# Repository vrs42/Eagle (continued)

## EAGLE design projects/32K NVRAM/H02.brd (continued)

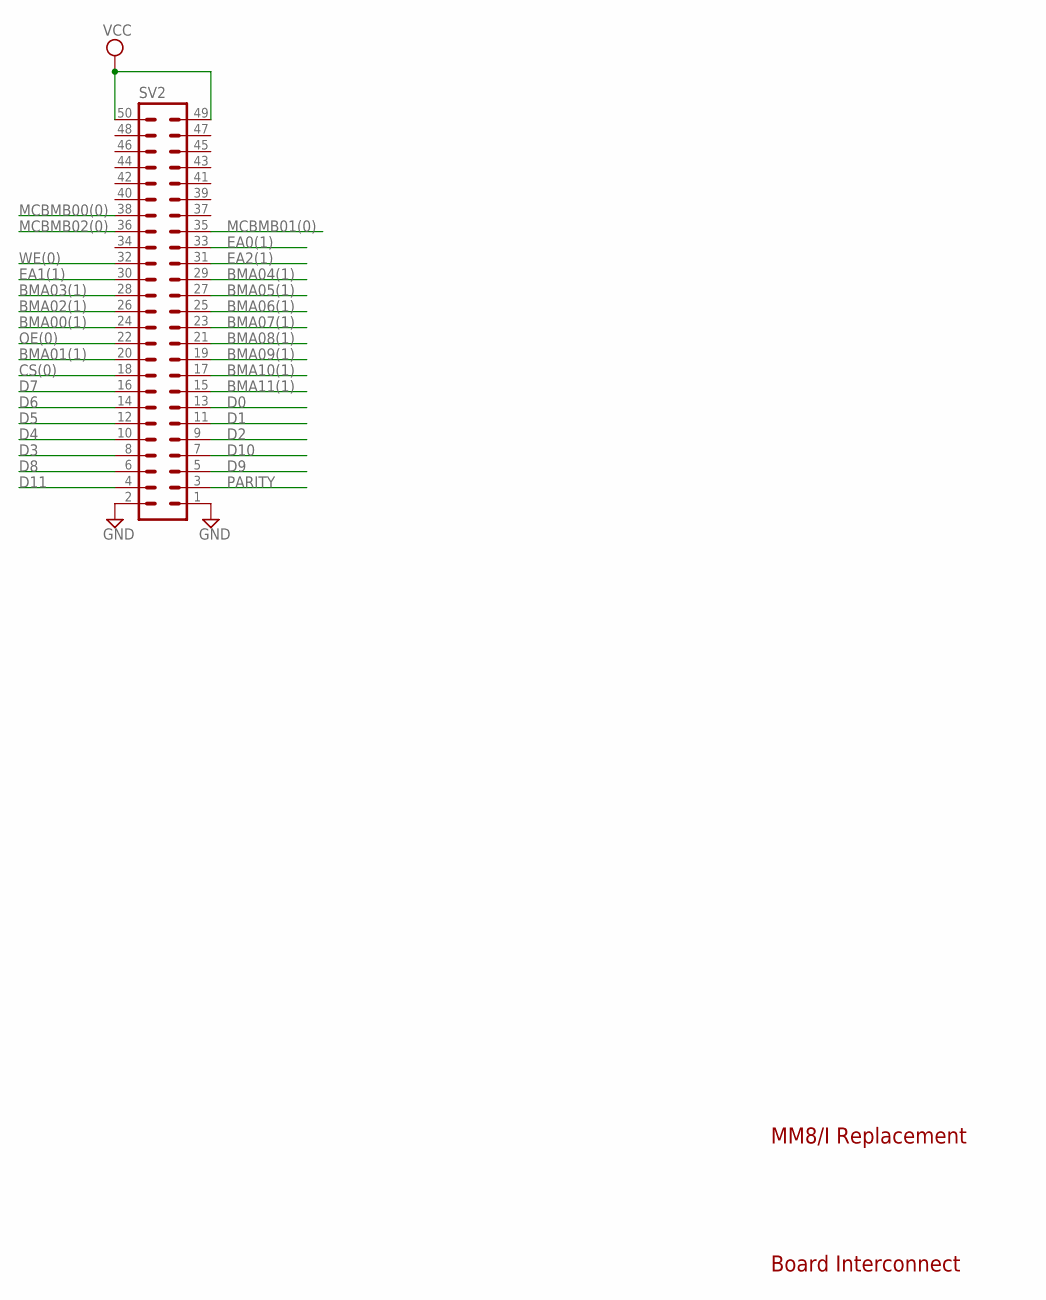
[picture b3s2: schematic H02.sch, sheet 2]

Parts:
SV2: ML50L

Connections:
BMA00(1): SV2.24; also elsewhere on the board
BMA01(1): SV2.20; also elsewhere on the board
BMA02(1): SV2.26; also elsewhere on the board
BMA03(1): SV2.28; also elsewhere on the board
BMA04(1): SV2.29; also elsewhere on the board
BMA05(1): SV2.27; also elsewhere on the board
BMA06(1): SV2.25; also elsewhere on the board
BMA07(1): SV2.23; also elsewhere on the board
BMA08(1): SV2.21; also elsewhere on the board
BMA09(1): SV2.19; also elsewhere on the board
BMA10(1): SV2.17; also elsewhere on the board
BMA11(1): SV2.15; also elsewhere on the board
CS(0): SV2.18; also elsewhere on the board
D0: SV2.13; also elsewhere on the board
D1: SV2.11; also elsewhere on the board
D2: SV2.9; also elsewhere on the board
D3: SV2.8; also elsewhere on the board
D4: SV2.10; also elsewhere on the board
D5: SV2.12; also elsewhere on the board
D6: SV2.14; also elsewhere on the board
D7: SV2.16; also elsewhere on the board
D8: SV2.6; also elsewhere on the board
D9: SV2.5; also elsewhere on the board
D10: SV2.7; also elsewhere on the board
D11: SV2.4; also elsewhere on the board
EA0(1): SV2.33; also elsewhere on the board
EA1(1): SV2.30; also elsewhere on the board
EA2(1): SV2.31; also elsewhere on the board
GND: SV2.1, SV2.2; also elsewhere on the board
MCBMB00(0): SV2.38; also elsewhere on the board
MCBMB01(0): SV2.35; also elsewhere on the board
MCBMB02(0): SV2.36; also elsewhere on the board
OE(0): SV2.22; also elsewhere on the board
PARITY: SV2.3; also elsewhere on the board
VCC: SV2.49, SV2.50; also elsewhere on the board
WE(0): SV2.32; also elsewhere on the board

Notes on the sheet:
Board Interconnect
MM8/I Replacement

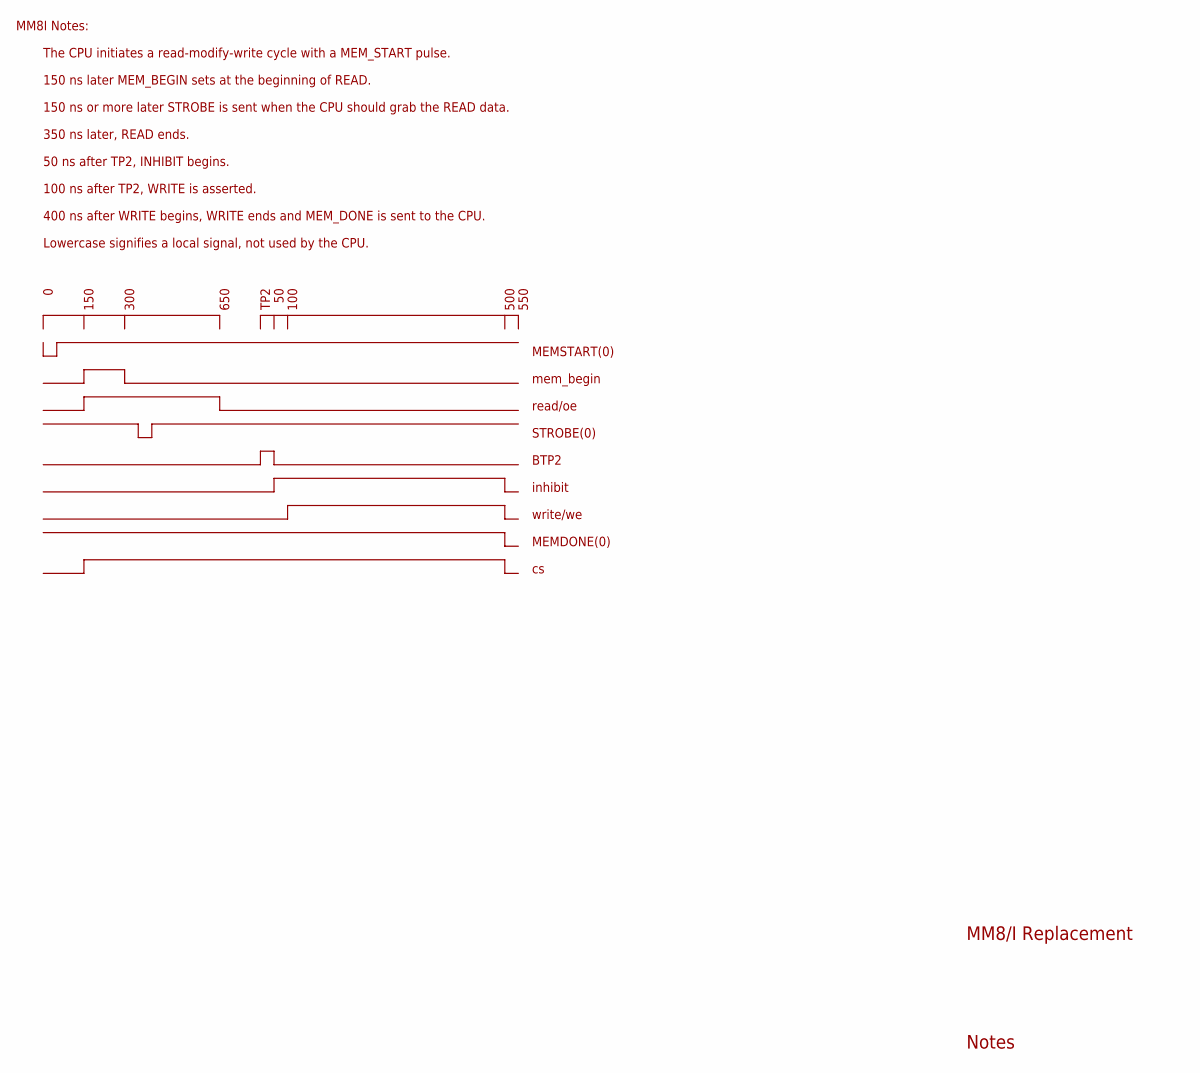
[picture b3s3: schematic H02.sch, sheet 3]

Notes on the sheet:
Notes
The CPU initiates a read-modify-write cycle with a MEM_START pulse.
150 ns later MEM_BEGIN sets at the beginning of READ.
150 ns or more later STROBE is sent when the CPU should grab the READ data.
50 ns after TP2, INHIBIT begins.
100 ns after TP2, WRITE is asserted.
400 ns after WRITE begins, WRITE ends and MEM_DONE is sent to the CPU.
350 ns later, READ ends.
150
300
650
TP2
100
500
MEMSTART(0)
mem_begin
read/oe
STROBE(0)
BTP2
inhibit
write/we
MEMDONE(0)
Lowercase signifies a local signal, not used by the CPU.
550
MM8I Notes:
MM8/I Replacement

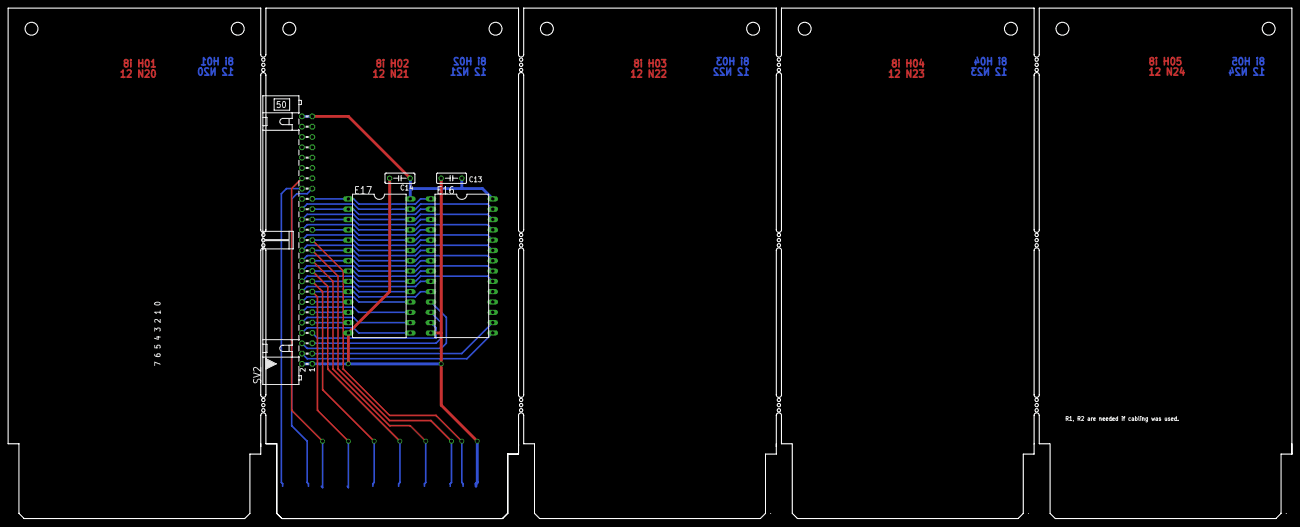
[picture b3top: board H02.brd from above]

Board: 2 copper layers, 316.2 x 125.7 mm, 7 parts (0 on the bottom side), 36 nets.

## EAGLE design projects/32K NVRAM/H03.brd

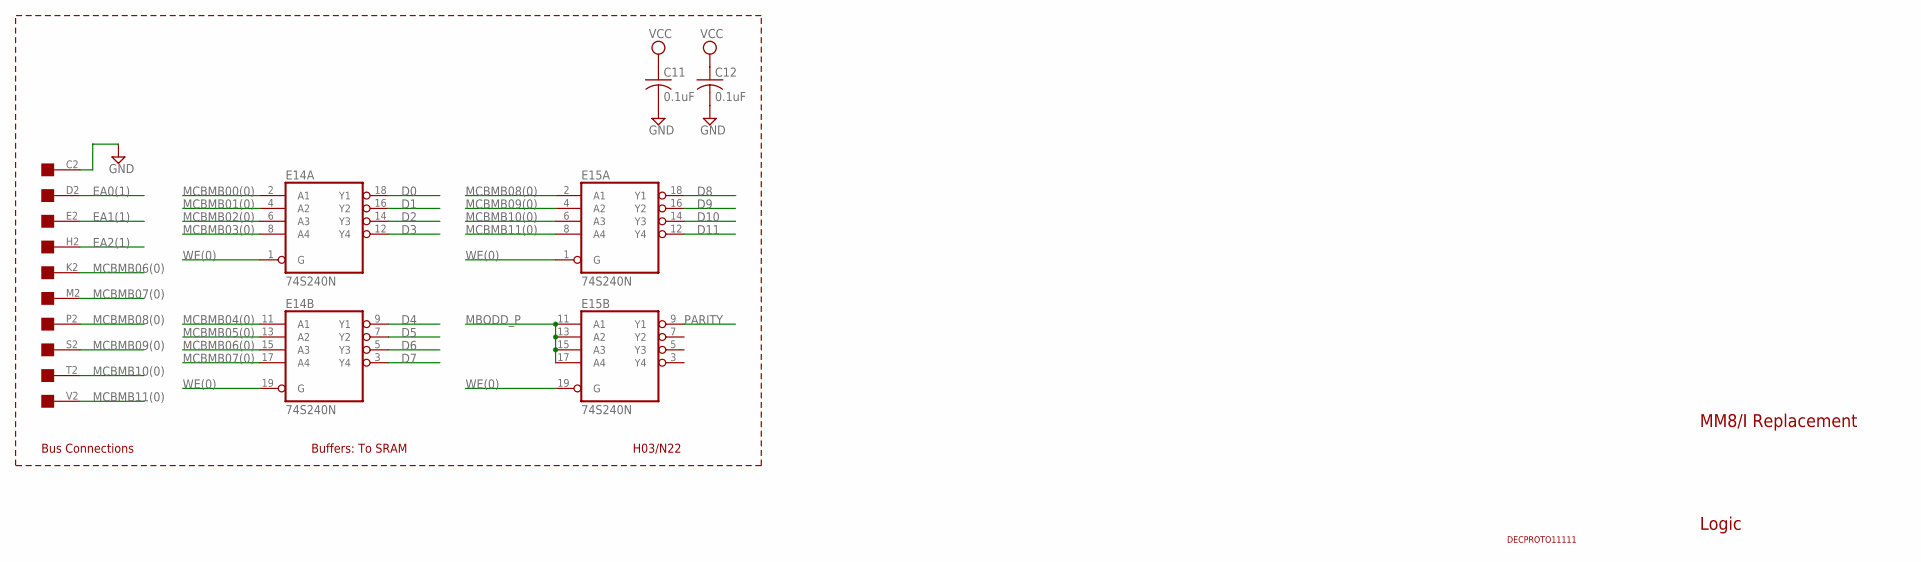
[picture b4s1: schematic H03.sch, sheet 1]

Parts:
C11, C12: 0.1uF; C050-025X075
E14, E15: 74S240N; DIL20
H03: EDGE-CON1
U$6: DECPROTO11111

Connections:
D0: E14.18 (Y1); also elsewhere on the board
D1: E14.16 (Y2); also elsewhere on the board
D2: E14.14 (Y3); also elsewhere on the board
D3: E14.12 (Y4); also elsewhere on the board
D4: E14.9 (Y1); also elsewhere on the board
D5: E14.7 (Y2); also elsewhere on the board
D6: E14.5 (Y3); also elsewhere on the board
D7: E14.3 (Y4); also elsewhere on the board
D8: E15.18 (Y1); also elsewhere on the board
D9: E15.16 (Y2); also elsewhere on the board
D10: E15.14 (Y3); also elsewhere on the board
D11: E15.12 (Y4); also elsewhere on the board
EA0(1): H03.D2; also elsewhere on the board
EA1(1): H03.E2; also elsewhere on the board
EA2(1): H03.H2; also elsewhere on the board
GND: C11.2, C12.2, E14.10 (GND), E15.10 (GND), H03.C2; also elsewhere on the board
MBODD_P: E15.11 (A1), E15.13 (A2), E15.15 (A3), E15.17 (A4); also elsewhere on the board
MCBMB00(0): E14.2 (A1); also elsewhere on the board
MCBMB01(0): E14.4 (A2); also elsewhere on the board
MCBMB02(0): E14.6 (A3); also elsewhere on the board
MCBMB03(0): E14.8 (A4); also elsewhere on the board
MCBMB04(0): E14.11 (A1); also elsewhere on the board
MCBMB05(0): E14.13 (A2); also elsewhere on the board
MCBMB06(0): E14.15 (A3), H03.K2
MCBMB07(0): E14.17 (A4), H03.M2
MCBMB08(0): E15.2 (A1), H03.P2
MCBMB09(0): E15.4 (A2), H03.S2
MCBMB10(0): E15.6 (A3), H03.T2
MCBMB11(0): E15.8 (A4), H03.V2
PARITY: E15.9 (Y1); also elsewhere on the board
VCC: C11.1, C12.1, E14.20 (VCC), E15.20 (VCC); also elsewhere on the board
WE(0): E14.1 (G), E14.19 (G), E15.1 (G), E15.19 (G); also elsewhere on the board

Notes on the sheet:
H03/N22
MM8/I Replacement
Buffers: To SRAM
Logic
Bus Connections

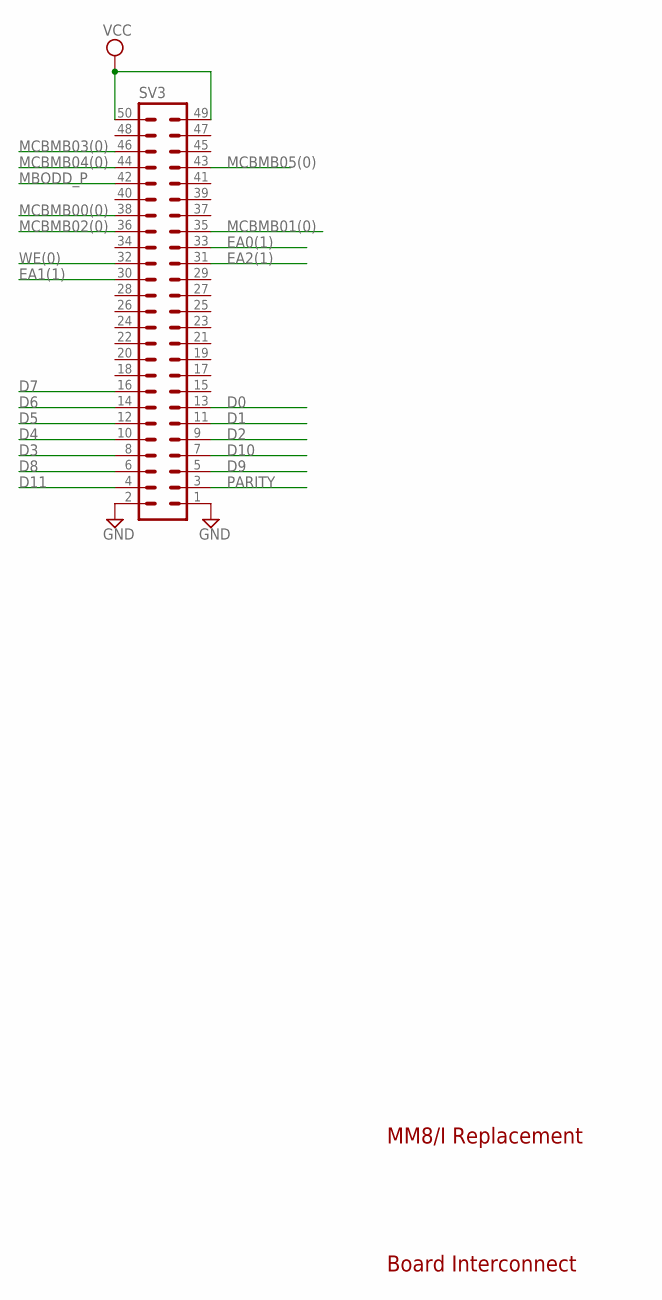
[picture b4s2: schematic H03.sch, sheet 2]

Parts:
SV3: ML50L

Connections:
D0: SV3.13; also elsewhere on the board
D1: SV3.11; also elsewhere on the board
D2: SV3.9; also elsewhere on the board
D3: SV3.8; also elsewhere on the board
D4: SV3.10; also elsewhere on the board
D5: SV3.12; also elsewhere on the board
D6: SV3.14; also elsewhere on the board
D7: SV3.16; also elsewhere on the board
D8: SV3.6; also elsewhere on the board
D9: SV3.5; also elsewhere on the board
D10: SV3.7; also elsewhere on the board
D11: SV3.4; also elsewhere on the board
EA0(1): SV3.33; also elsewhere on the board
EA1(1): SV3.30; also elsewhere on the board
EA2(1): SV3.31; also elsewhere on the board
GND: SV3.1, SV3.2; also elsewhere on the board
MBODD_P: SV3.42; also elsewhere on the board
MCBMB00(0): SV3.38; also elsewhere on the board
MCBMB01(0): SV3.35; also elsewhere on the board
MCBMB02(0): SV3.36; also elsewhere on the board
MCBMB03(0): SV3.46; also elsewhere on the board
MCBMB04(0): SV3.44; also elsewhere on the board
MCBMB05(0): SV3.43; also elsewhere on the board
PARITY: SV3.3; also elsewhere on the board
VCC: SV3.49, SV3.50; also elsewhere on the board
WE(0): SV3.32; also elsewhere on the board

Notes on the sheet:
Board Interconnect
MM8/I Replacement

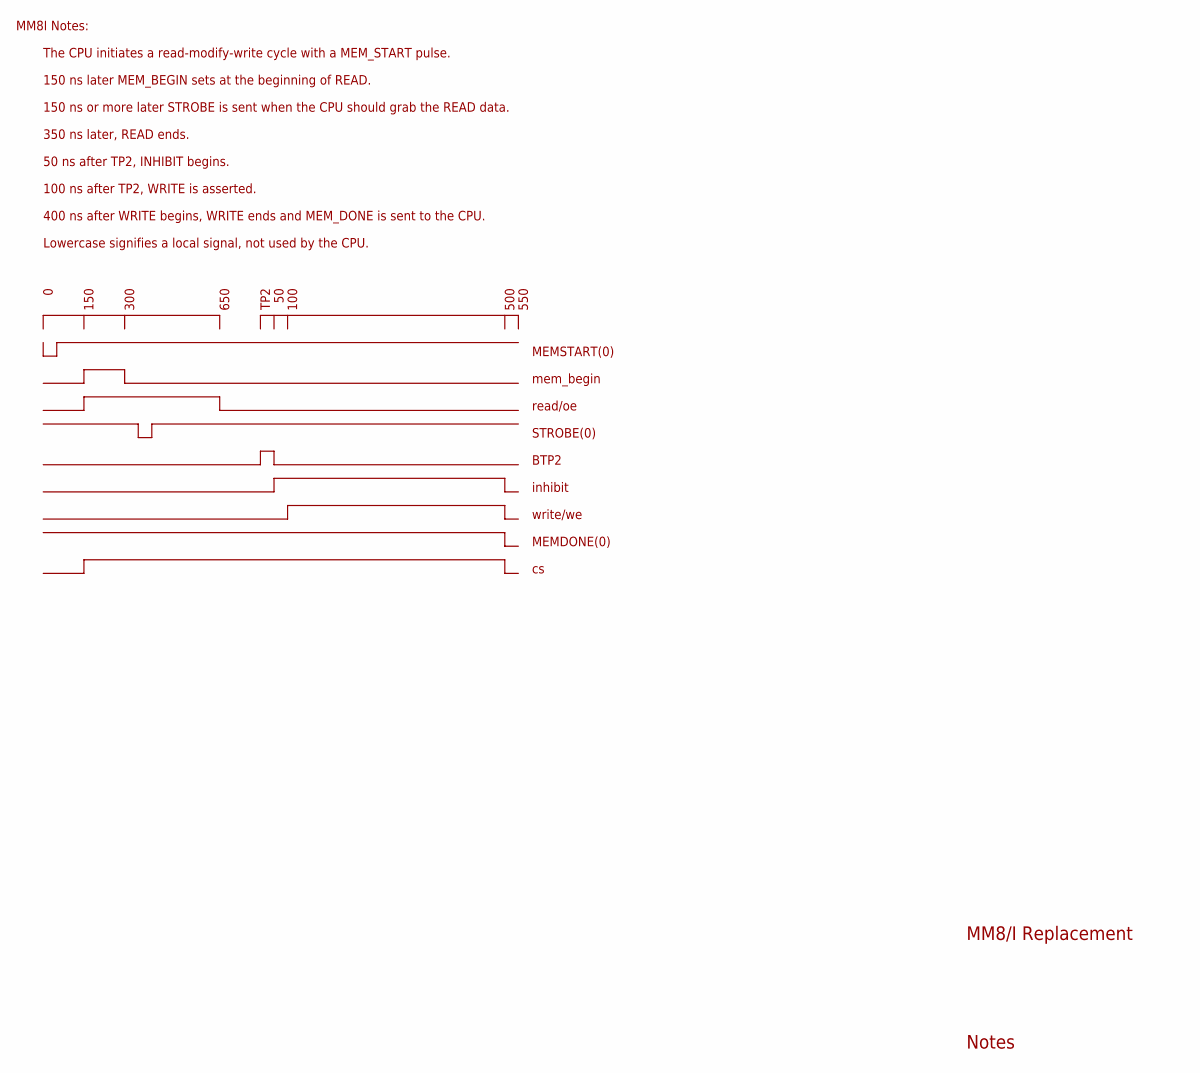
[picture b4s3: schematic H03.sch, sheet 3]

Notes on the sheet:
Notes
The CPU initiates a read-modify-write cycle with a MEM_START pulse.
150 ns later MEM_BEGIN sets at the beginning of READ.
150 ns or more later STROBE is sent when the CPU should grab the READ data.
50 ns after TP2, INHIBIT begins.
100 ns after TP2, WRITE is asserted.
400 ns after WRITE begins, WRITE ends and MEM_DONE is sent to the CPU.
350 ns later, READ ends.
150
300
650
TP2
100
500
MEMSTART(0)
mem_begin
read/oe
STROBE(0)
BTP2
inhibit
write/we
MEMDONE(0)
Lowercase signifies a local signal, not used by the CPU.
550
MM8I Notes:
MM8/I Replacement

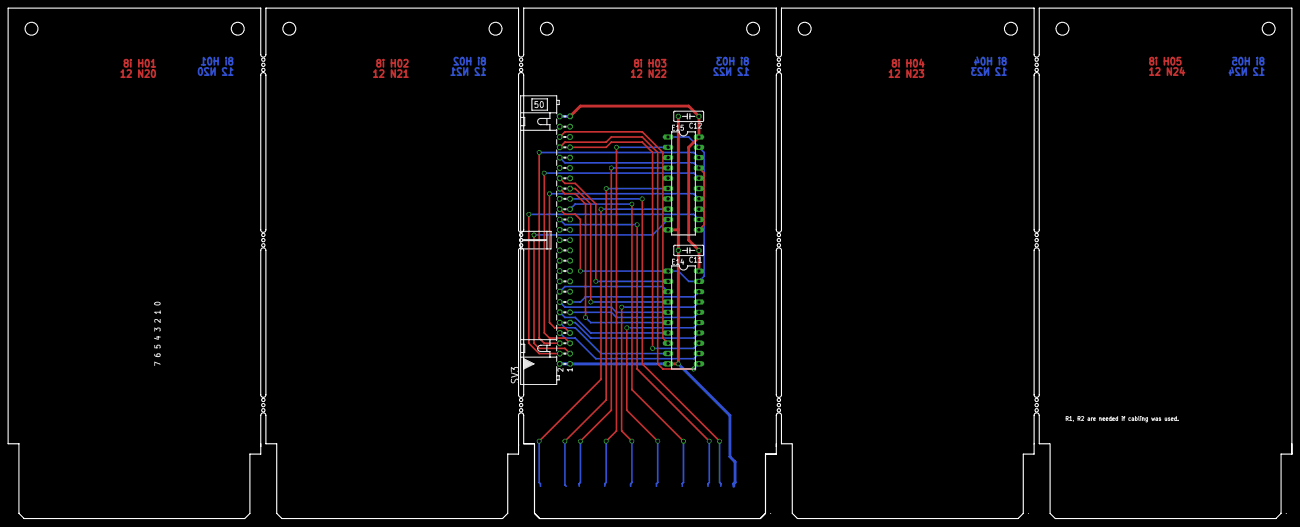
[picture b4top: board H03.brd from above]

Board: 2 copper layers, 316.2 x 125.7 mm, 7 parts (0 on the bottom side), 32 nets.

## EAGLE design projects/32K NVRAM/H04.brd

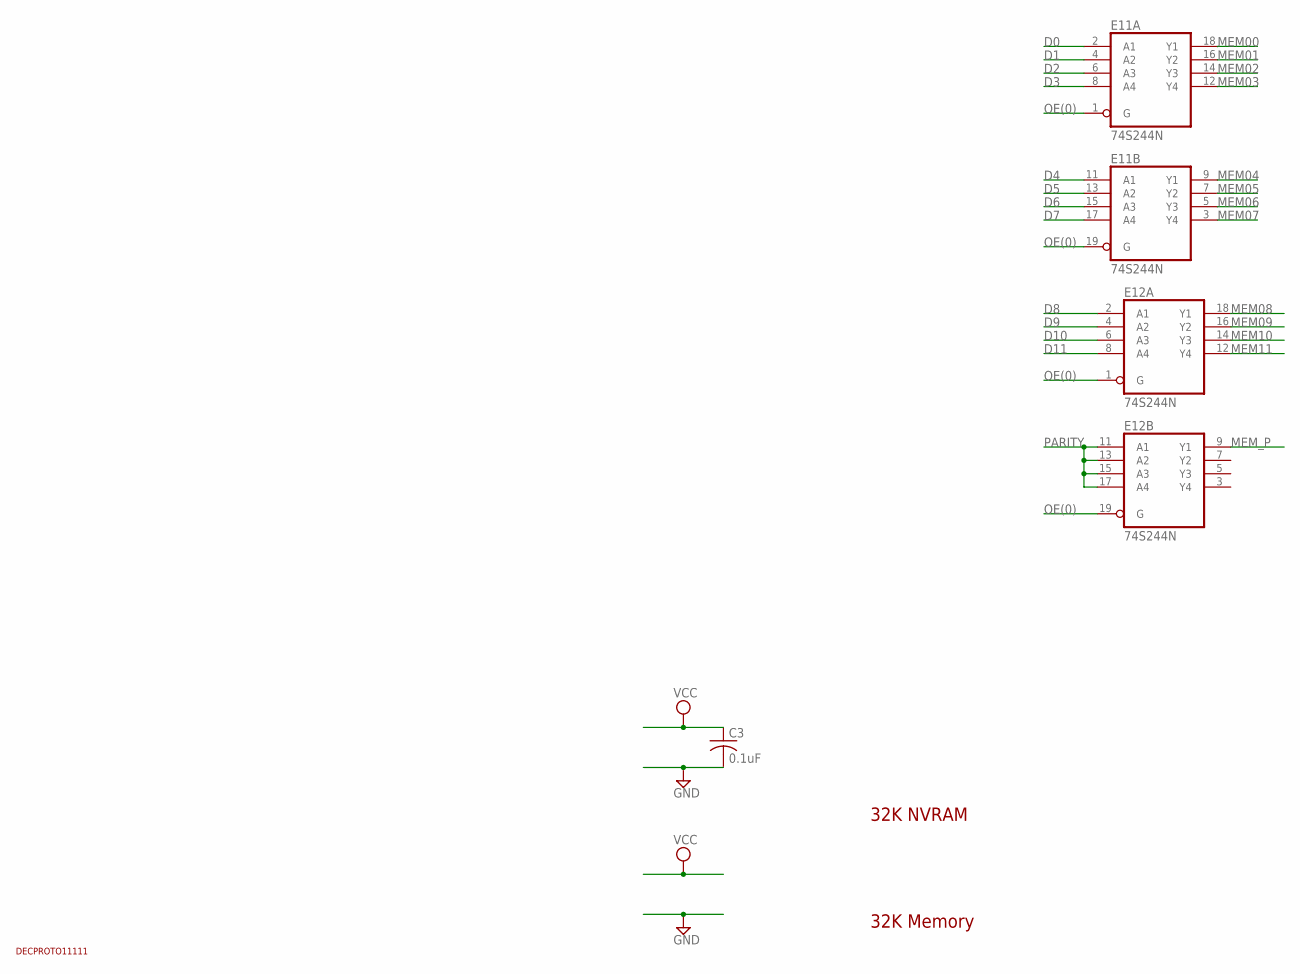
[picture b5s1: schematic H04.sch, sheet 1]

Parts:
C3: 0.1uF; C050-025X075
E11, E12: 74S244N; DIL20
U$6: DECPROTO11111

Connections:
D0: E11.2 (A1); also elsewhere on the board
D1: E11.4 (A2); also elsewhere on the board
D2: E11.6 (A3); also elsewhere on the board
D3: E11.8 (A4); also elsewhere on the board
D4: E11.11 (A1); also elsewhere on the board
D5: E11.13 (A2); also elsewhere on the board
D6: E11.15 (A3); also elsewhere on the board
D7: E11.17 (A4); also elsewhere on the board
D8: E12.2 (A1); also elsewhere on the board
D9: E12.4 (A2); also elsewhere on the board
D10: E12.6 (A3); also elsewhere on the board
D11: E12.8 (A4); also elsewhere on the board
GND: C3.2, E11.10 (GND), E12.10 (GND); also elsewhere on the board
MEM00: E11.18 (Y1); also elsewhere on the board
MEM01: E11.16 (Y2); also elsewhere on the board
MEM02: E11.14 (Y3); also elsewhere on the board
MEM03: E11.12 (Y4); also elsewhere on the board
MEM04: E11.9 (Y1); also elsewhere on the board
MEM05: E11.7 (Y2); also elsewhere on the board
MEM06: E11.5 (Y3); also elsewhere on the board
MEM07: E11.3 (Y4); also elsewhere on the board
MEM08: E12.18 (Y1); also elsewhere on the board
MEM09: E12.16 (Y2); also elsewhere on the board
MEM10: E12.14 (Y3); also elsewhere on the board
MEM11: E12.12 (Y4); also elsewhere on the board
MEM_P: E12.9 (Y1); also elsewhere on the board
OE(0): E11.1 (G), E11.19 (G), E12.1 (G), E12.19 (G); also elsewhere on the board
PARITY: E12.11 (A1), E12.13 (A2), E12.15 (A3), E12.17 (A4); also elsewhere on the board
VCC: C3.1, E11.20 (VCC), E12.20 (VCC); also elsewhere on the board

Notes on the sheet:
32K NVRAM
32K Memory

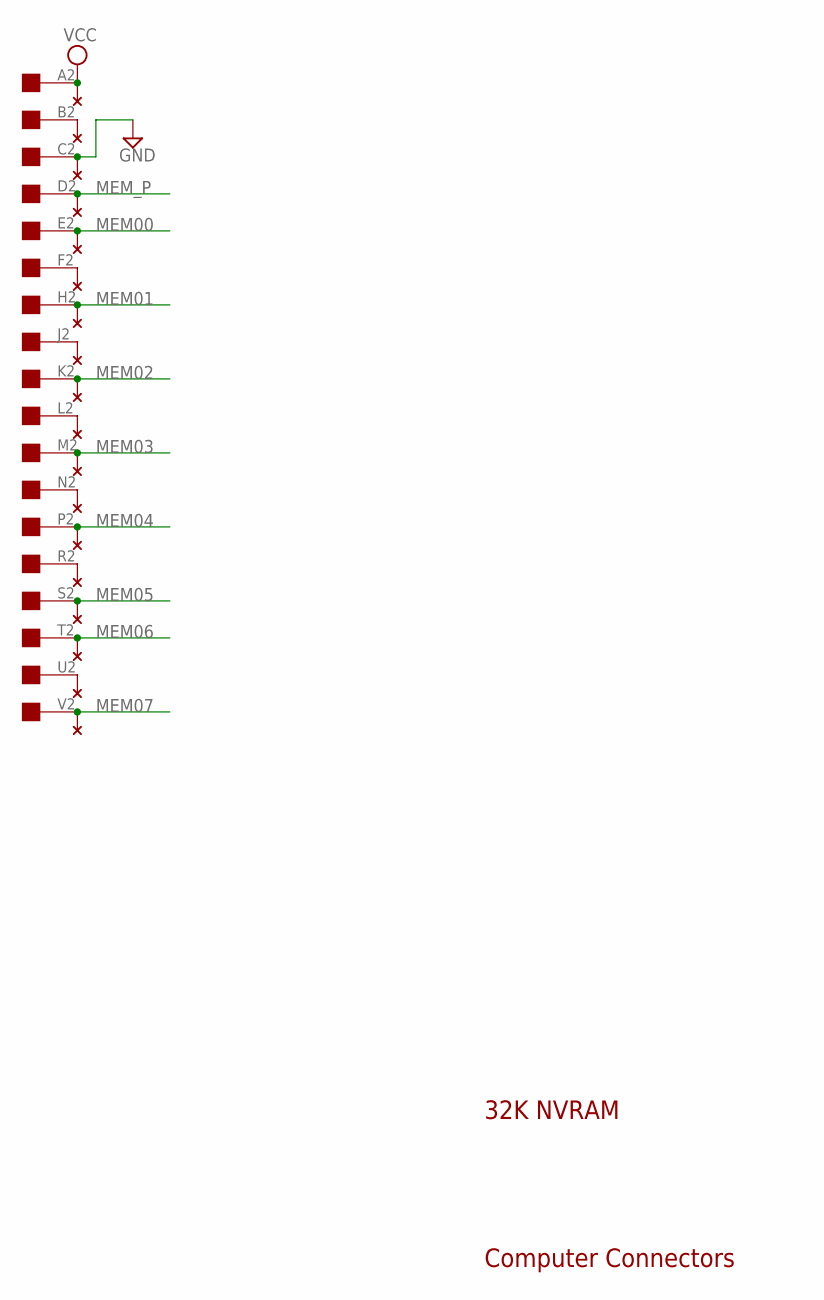
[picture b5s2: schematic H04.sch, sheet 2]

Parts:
H04: EDGE-CON1
U$4: THRU-HOLE2; THRU-HOLEB

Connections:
GND: H04.C2, U$4.C2; also elsewhere on the board
MEM00: H04.E2, U$4.E2; also elsewhere on the board
MEM01: H04.H2, U$4.H2; also elsewhere on the board
MEM02: H04.K2, U$4.K2; also elsewhere on the board
MEM03: H04.M2, U$4.M2; also elsewhere on the board
MEM04: H04.P2, U$4.P2; also elsewhere on the board
MEM05: H04.S2, U$4.S2; also elsewhere on the board
MEM06: H04.T2, U$4.T2; also elsewhere on the board
MEM07: H04.V2, U$4.V2; also elsewhere on the board
MEM_P: H04.D2, U$4.D2; also elsewhere on the board
unnamed: H04.J2, U$4.J2
unnamed: H04.L2, U$4.L2
unnamed: H04.N2, U$4.N2
unnamed: H04.F2, U$4.F2
unnamed: H04.R2, U$4.R2
unnamed: H04.B2, U$4.B2
unnamed: H04.U2, U$4.U2
VCC: H04.A2, U$4.A2; also elsewhere on the board

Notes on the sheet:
32K NVRAM
Computer Connectors

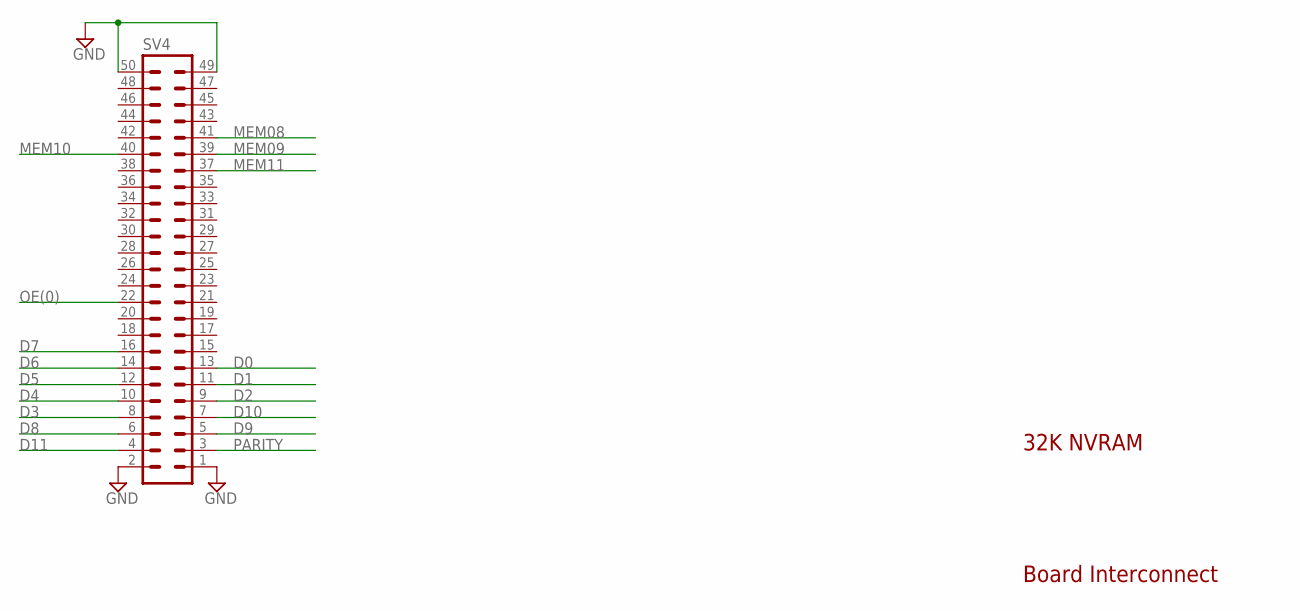
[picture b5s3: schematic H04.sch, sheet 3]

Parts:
SV4: ML50L

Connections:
D0: SV4.13; also elsewhere on the board
D1: SV4.11; also elsewhere on the board
D2: SV4.9; also elsewhere on the board
D3: SV4.8; also elsewhere on the board
D4: SV4.10; also elsewhere on the board
D5: SV4.12; also elsewhere on the board
D6: SV4.14; also elsewhere on the board
D7: SV4.16; also elsewhere on the board
D8: SV4.6; also elsewhere on the board
D9: SV4.5; also elsewhere on the board
D10: SV4.7; also elsewhere on the board
D11: SV4.4; also elsewhere on the board
GND: SV4.1, SV4.2, SV4.49, SV4.50; also elsewhere on the board
MEM08: SV4.41; also elsewhere on the board
MEM09: SV4.39; also elsewhere on the board
MEM10: SV4.40; also elsewhere on the board
MEM11: SV4.37; also elsewhere on the board
OE(0): SV4.22; also elsewhere on the board
PARITY: SV4.3; also elsewhere on the board

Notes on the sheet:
32K NVRAM
Board Interconnect

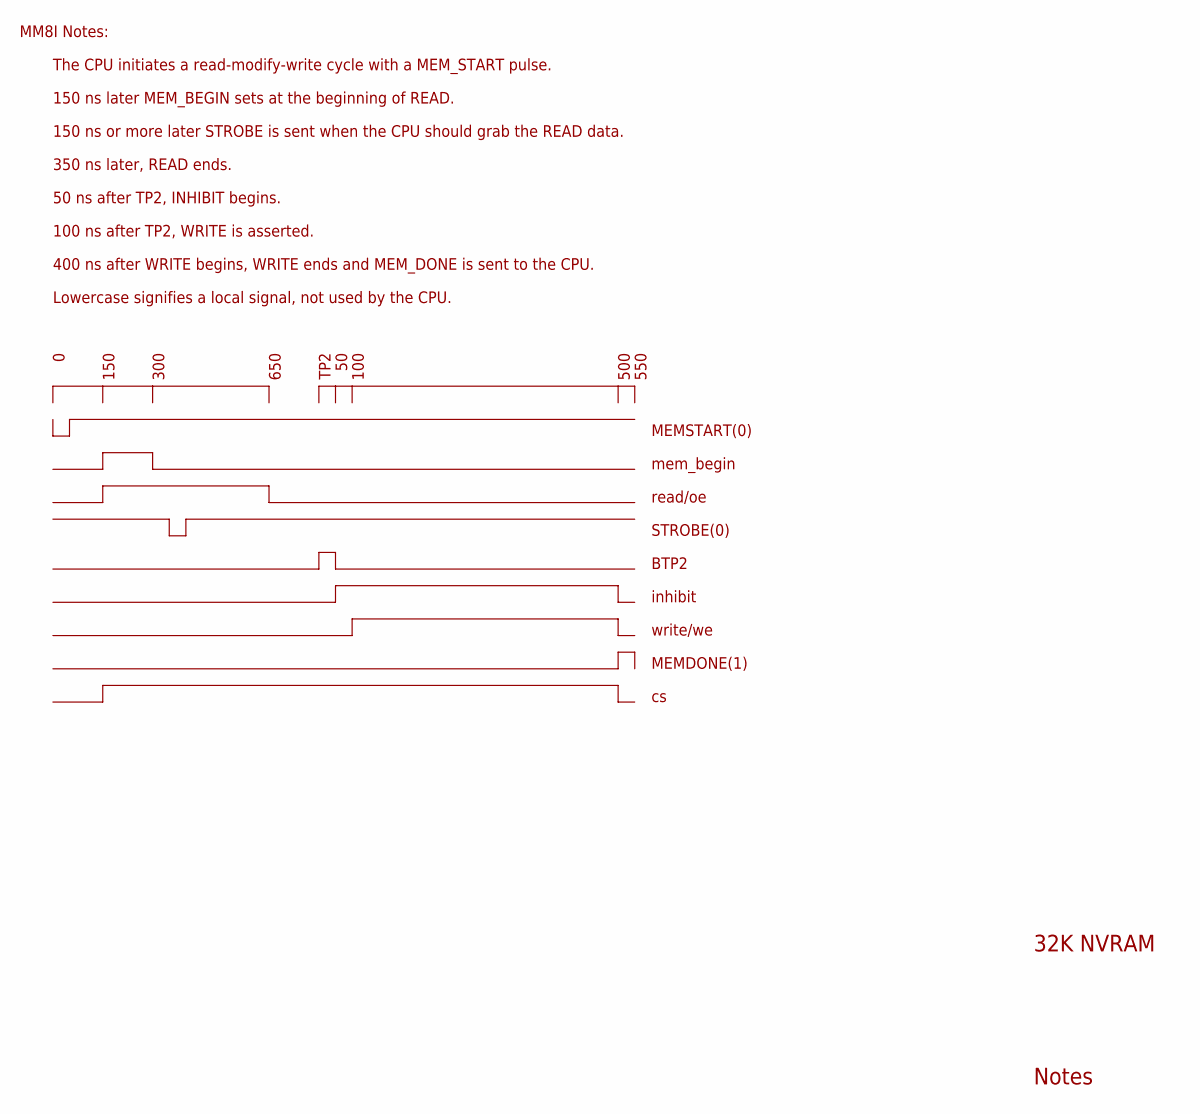
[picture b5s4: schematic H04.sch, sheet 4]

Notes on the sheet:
32K NVRAM
Notes
The CPU initiates a read-modify-write cycle with a MEM_START pulse.
150 ns later MEM_BEGIN sets at the beginning of READ.
150 ns or more later STROBE is sent when the CPU should grab the READ data.
50 ns after TP2, INHIBIT begins.
100 ns after TP2, WRITE is asserted.
400 ns after WRITE begins, WRITE ends and MEM_DONE is sent to the CPU.
350 ns later, READ ends.
150
300
650
TP2
100
500
MEMSTART(0)
mem_begin
read/oe
STROBE(0)
BTP2
inhibit
write/we
MEMDONE(1)
Lowercase signifies a local signal, not used by the CPU.
550
MM8I Notes:

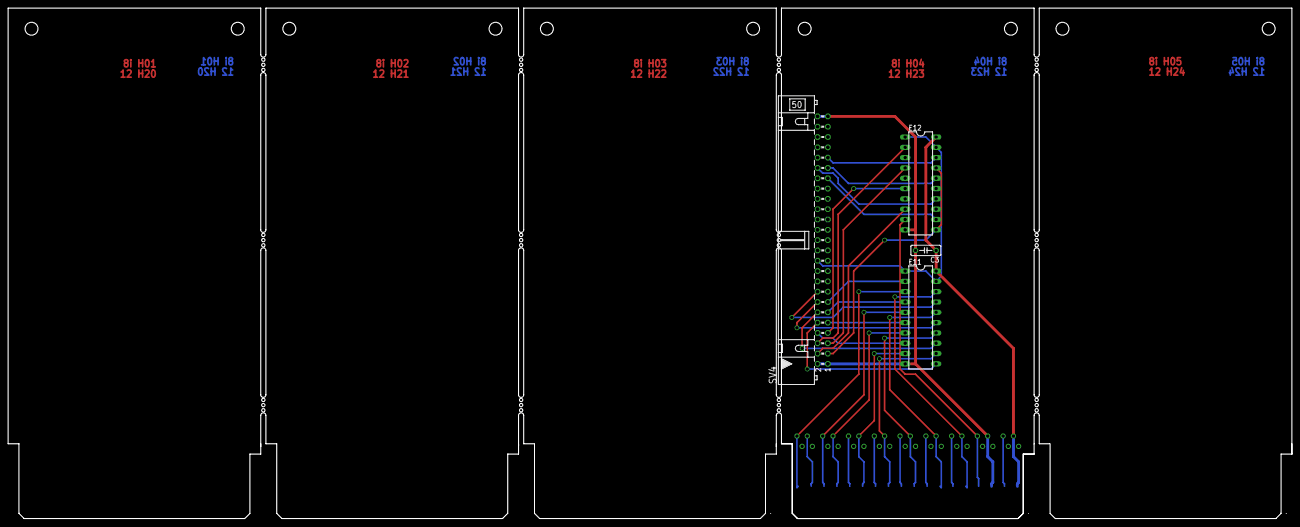
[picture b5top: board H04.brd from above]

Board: 2 copper layers, 316.2 x 125.7 mm, 7 parts (0 on the bottom side), 36 nets.

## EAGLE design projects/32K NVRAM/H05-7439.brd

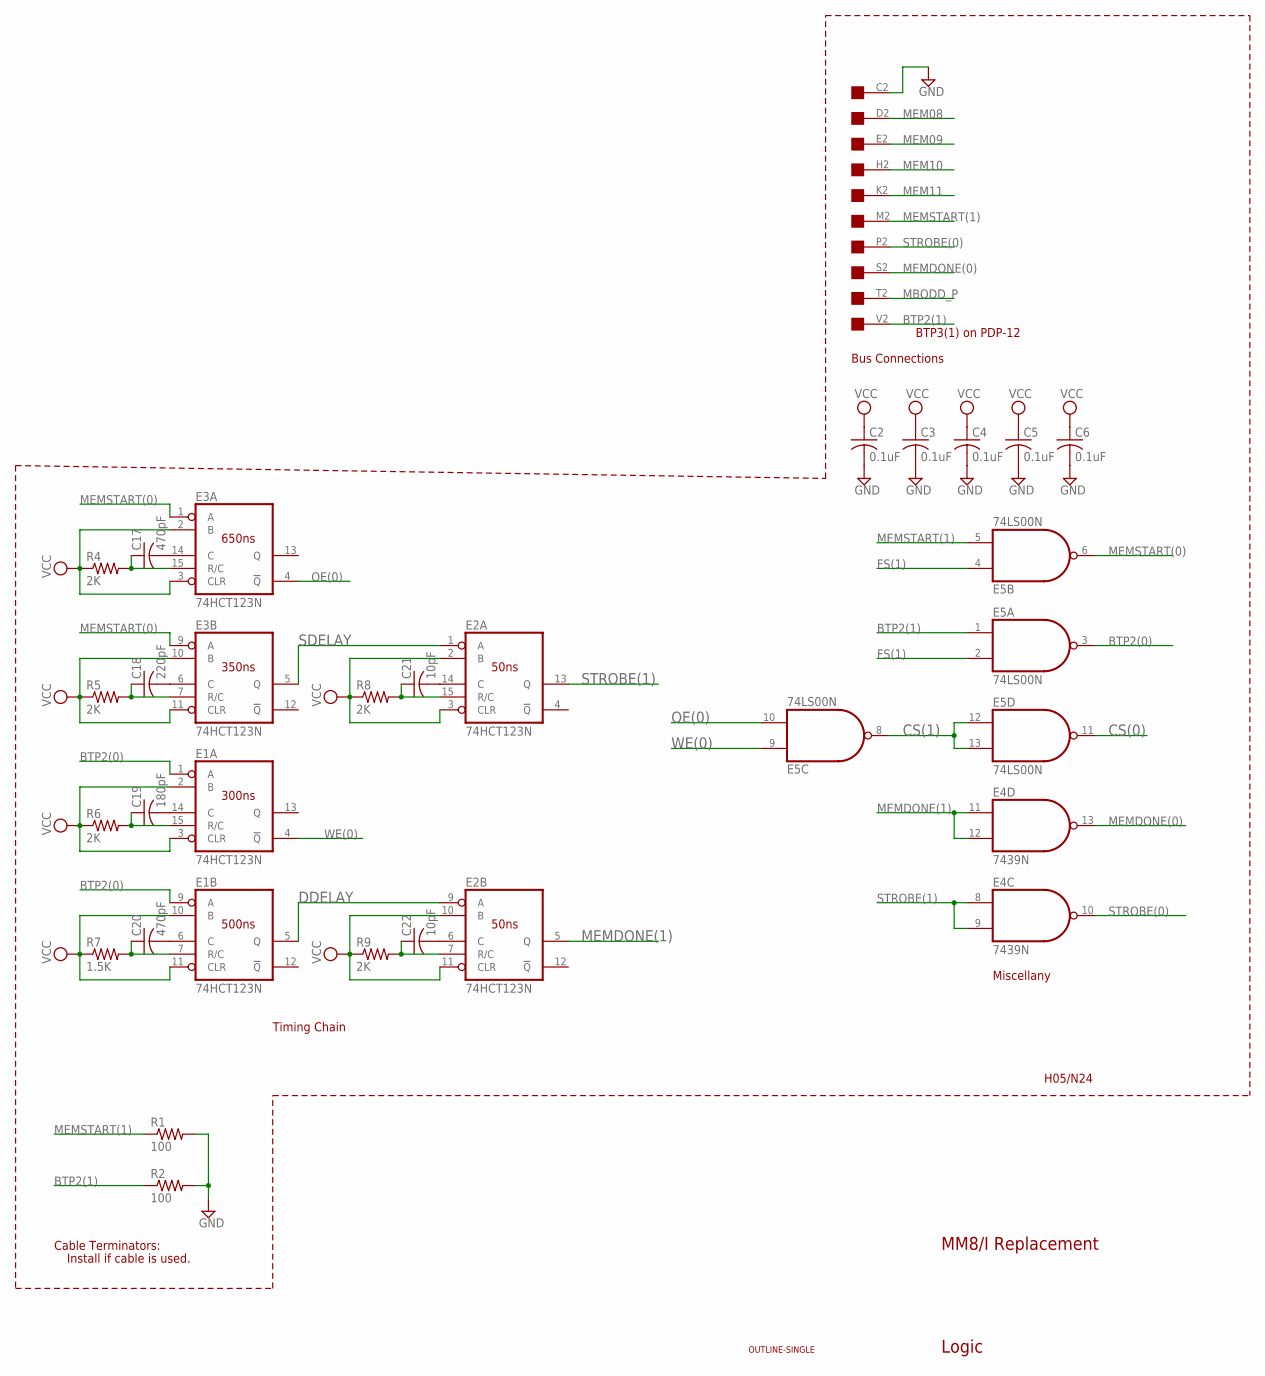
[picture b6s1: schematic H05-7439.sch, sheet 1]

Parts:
C2, C3, C4, C5, C6: 0.1uF; C050-025X075
C17, C20: 470pF; C050-025X075
C18: 220pF; C050-025X075
C19: 180pF; C050-025X075
C21, C22: 10pF; C050-025X075
E1, E2, E3: 74HCT123N; DIL16
E4: 7439N; DIL14
E5: 74LS00N; DIL14
H05: EDGE-CON1
R1, R2: 100; 0207/10
R4, R5, R6, R8, R9: 2K; 0207/10
R7: 1.5K; 0207/10
U$1: OUTLINE-SINGLE; SINGLE

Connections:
BTP2(0): E1.1 (A), E1.9 (A), E5.3 (O)
BTP2(1): E5.1 (I0), H05.V2, R2.1
CS(0): E5.11 (O); also elsewhere on the board
CS(1): E5.8 (O), E5.12 (I0), E5.13 (I1)
DDELAY: E1.5 (Q), E2.9 (A)
FS(1): E5.2 (I1), E5.4 (I0); also elsewhere on the board
GND: C2.2, C3.2, C4.2, C5.2, C6.2, E1.8 (GND), E2.8 (GND), E3.8 (GND), E4.7 (GND), E5.7 (GND), H05.C2, R1.2, R2.2; also elsewhere on the board
MBODD_P: H05.T2; also elsewhere on the board
MEM08: H05.D2; also elsewhere on the board
MEM09: H05.E2; also elsewhere on the board
MEM10: H05.H2; also elsewhere on the board
MEM11: H05.K2; also elsewhere on the board
MEMDONE(0): E4.13 (O), H05.S2
MEMDONE(1): E2.5 (Q), E4.11 (I0), E4.12 (I1)
MEMSTART(0): E3.1 (A), E3.9 (A), E5.6 (O)
MEMSTART(1): E5.5 (I1), H05.M2, R1.1
unnamed: C17.1, E3.15 (R/C), R4.2
unnamed: C17.2, E3.14 (C)
unnamed: C18.1, E3.7 (R/C), R5.2
unnamed: C18.2, E3.6 (C)
unnamed: C19.1, E1.15 (R/C), R6.2
unnamed: C19.2, E1.14 (C)
unnamed: C20.1, E1.7 (R/C), R7.2
unnamed: C20.2, E1.6 (C)
unnamed: C21.1, E2.15 (R/C), R8.2
unnamed: C21.2, E2.14 (C)
unnamed: C22.1, E2.7 (R/C), R9.2
unnamed: C22.2, E2.6 (C)
OE(0): E3.4 (!Q), E5.10 (I1); also elsewhere on the board
SDELAY: E2.1 (A), E3.5 (Q)
STROBE(0): E4.10 (O), H05.P2
STROBE(1): E2.13 (Q), E4.8 (I0), E4.9 (I1)
VCC: C2.1, C3.1, C4.1, C5.1, C6.1, E1.2 (B), E1.3 (CLR), E1.10 (B), E1.11 (CLR), E1.16 (VCC), E2.2 (B), E2.3 (CLR), E2.10 (B), E2.11 (CLR), E2.16 (VCC), E3.2 (B), E3.3 (CLR), E3.10 (B), E3.11 (CLR), E3.16 (VCC), E4.14 (VCC), E5.14 (VCC), R4.1, R5.1, R6.1, R7.1, R8.1, R9.1; also elsewhere on the board
WE(0): E1.4 (!Q), E5.9 (I0); also elsewhere on the board

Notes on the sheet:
MM8/I Replacement
Timing Chain
BTP3(1) on PDP-12
Miscellany
H05/N24
Logic
Bus Connections
Cable Terminators:
Install if cable is used.
650ns
350ns
50ns
300ns
500ns
